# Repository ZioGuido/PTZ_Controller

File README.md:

# PTZ_Controller
Project for controlling PTZ camera via Arduino 

This project uses a Raspberry Pi Pico, an UART TTL to RS485 transceiver and a bunch of buttons to control PTZ cameras using the Pelco-D protocol.
I started this project because I was unhappy with the original controller we bought for controlling PTZ cameras in our TV studio. 
Those joystick controllers are made for the CCTV suirvellance cameras, they're not practical for the TV studio when recording or streaming live.

There were a series of issues:
- Too many button pushes to select a camera address (ESC, ADDR, number, ENTER)
- Too many button pushes to recall a preset (ESC, PRESET, number, ENTER)
- Joystick isn't precise
- Pan and Tilt speeds ramp up too rapidly using the joystick
- Buttons are too noisy
- LCD backlight goes off after a short while and you don't know which camera address it's on until you push a boutton

For these reasons I decided to make my owh controller without using a joystick, only big buttons and a couple of potentiometers.
Unfortunately, the camera we're using don't recognize the Zoom speed parameter from Pelco-D protocol, I should try writing a similar code but with Visca.
But for the remaining points, this controller is way better: silent buttons, just one push to select a camera (up to 4 addresses), 
just one push to recall a preset (up to 6 per camera), and you can vary Pan & Tilt speed while panning or tilting in a very smooth way.

One more thing:
This project makes use of 74HC595 and 74HC165 shift registers for controlling LEDs and reading button inputs.
These are serialized and share one common clock line, with the advantage of managing a high number of buttons and LEDs using only 4 pins of the CPU board.

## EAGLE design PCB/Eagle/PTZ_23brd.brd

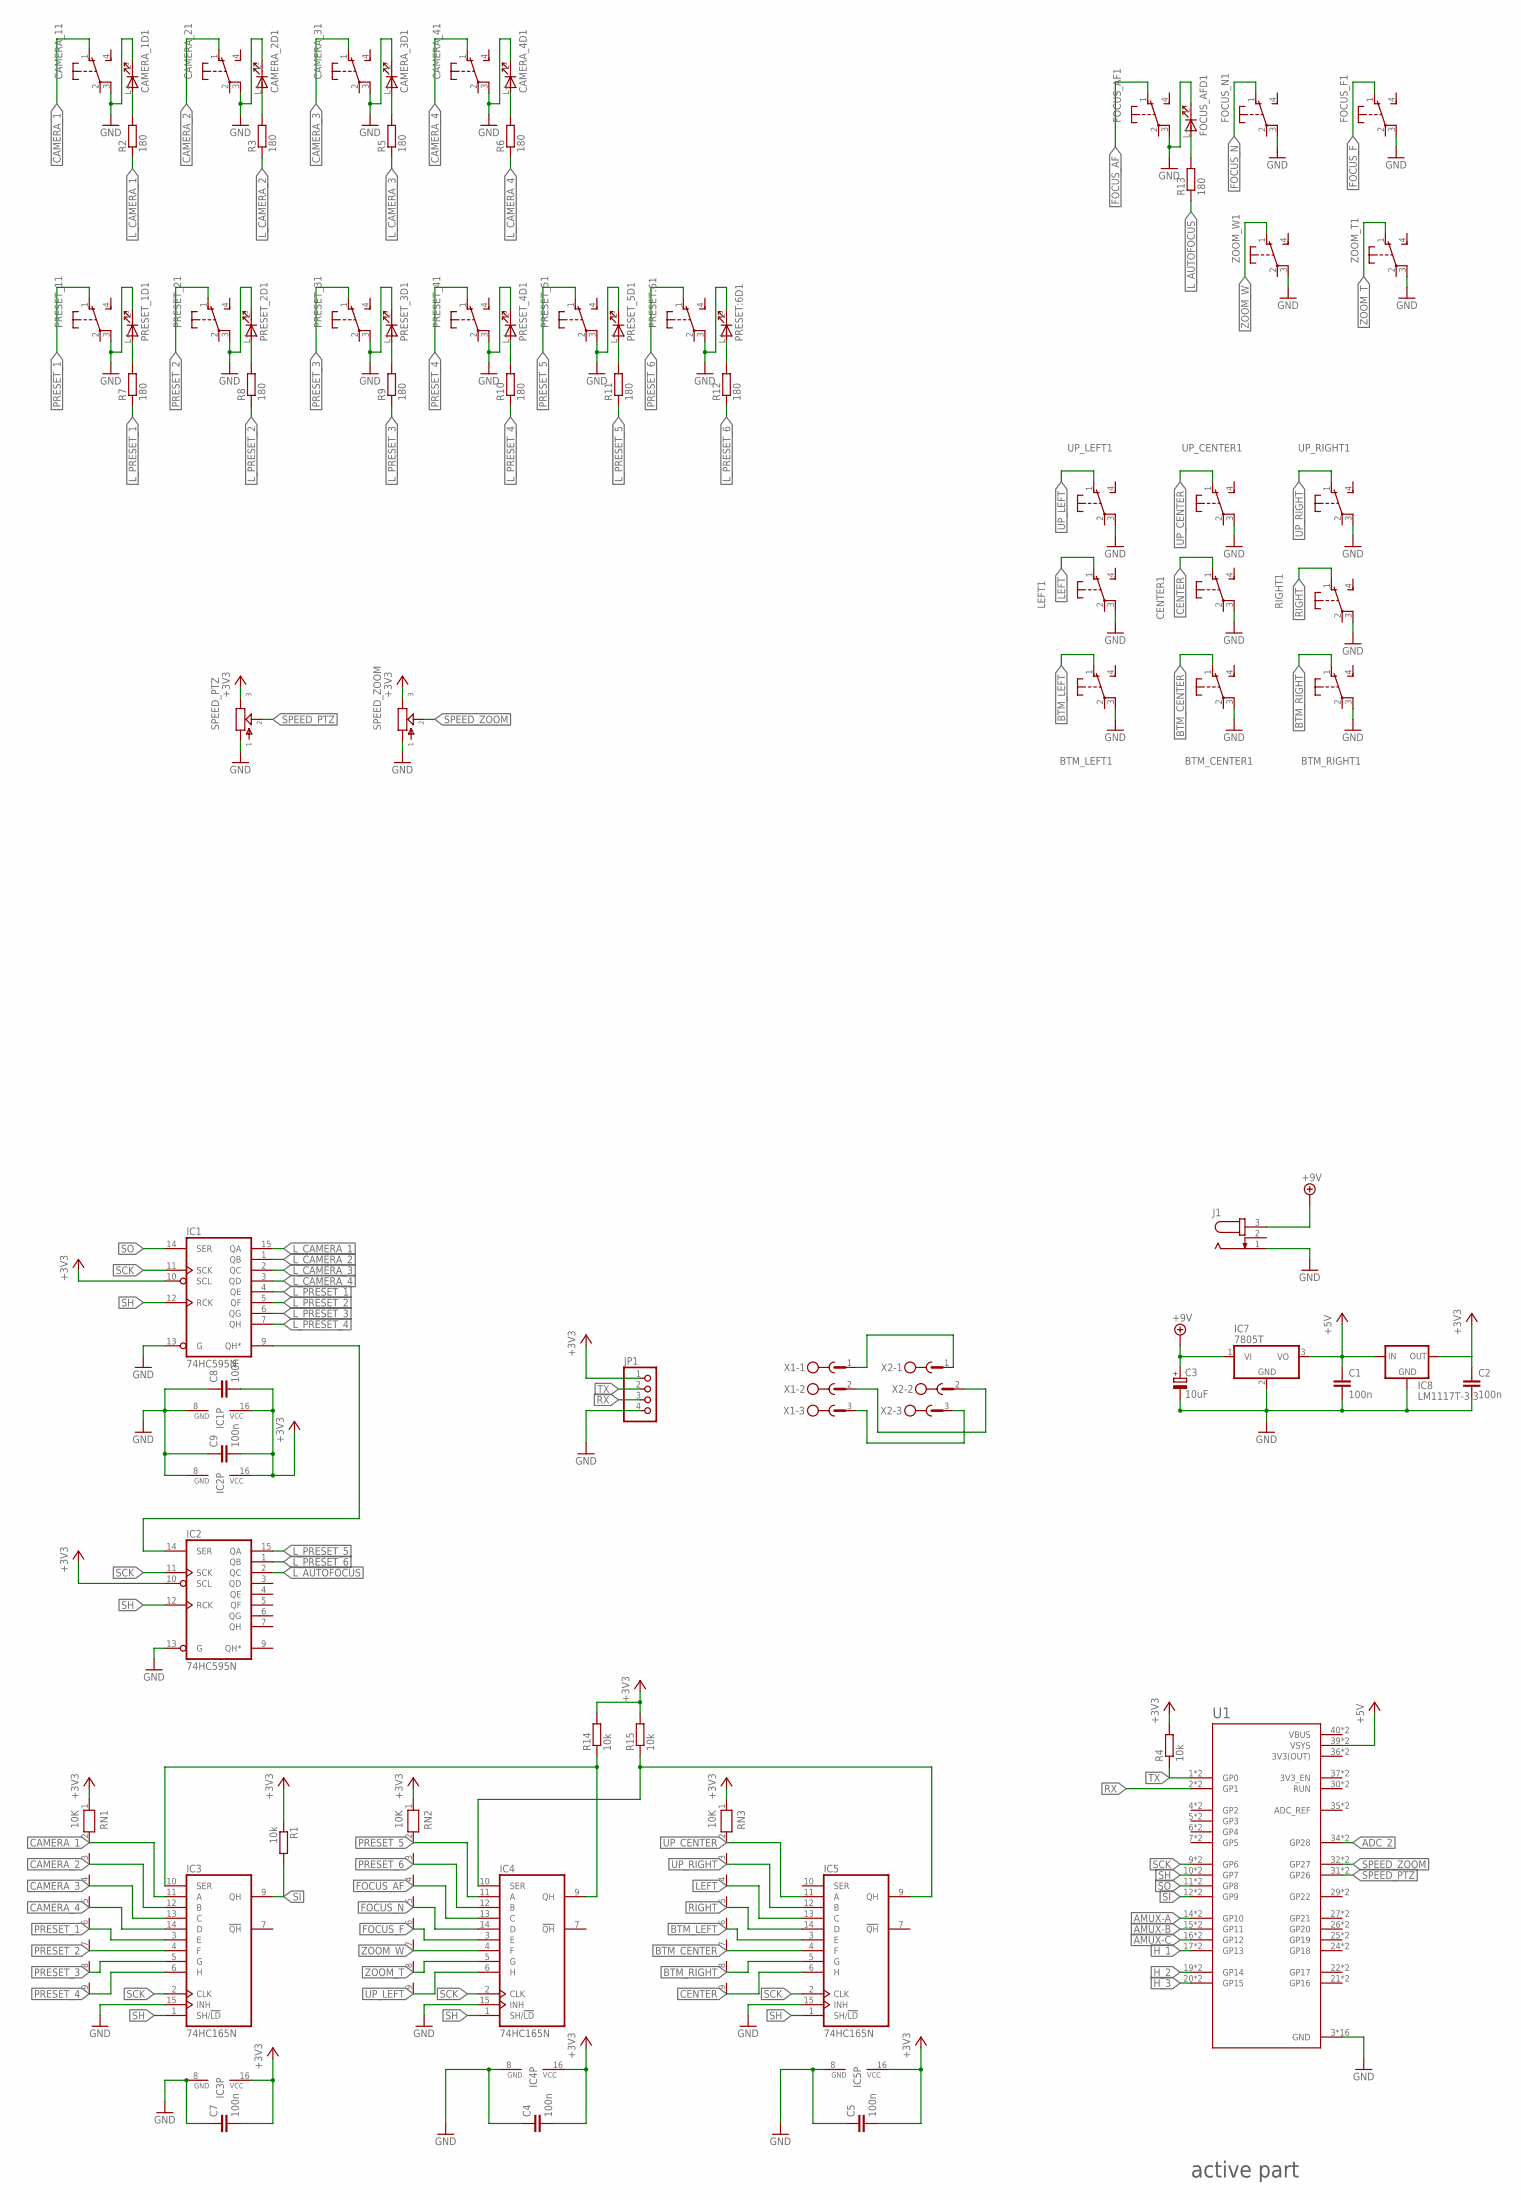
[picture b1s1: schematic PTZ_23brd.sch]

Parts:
BTM_CENTER: SWITCH-SHANPU_SRKLSHANPU_SPL; SWITCH-SHANPU_SPLG1YCS0014
BTM_LEFT: SWITCH-SHANPU_SRKLSHANPU_SPL; SWITCH-SHANPU_SPLG1YCS0014
BTM_RIGHT: SWITCH-SHANPU_SRKLSHANPU_SPL; SWITCH-SHANPU_SPLG1YCS0014
C1, C2, C4, C5, C7, C8, C9: 100n; C025-025X050
C3: 10uF; E2-5
CAMERA_1, CAMERA_2, CAMERA_3, CAMERA_4: SWITCH-SHANPU_SRKLSHANPU_SPL; SWITCH-SHANPU_SPLG1YCS0014
CENTER: SWITCH-SHANPU_SRKLSHANPU_SPL; SWITCH-SHANPU_SPLG1YCS0014
FOCUS_AF: SWITCH-SHANPU_SRKLSHANPU_SPL; SWITCH-SHANPU_SPLG1YCS0014
FOCUS_F: SWITCH-SHANPU_SRKLSHANPU_SPL; SWITCH-SHANPU_SPLG1YCS0014
FOCUS_N: SWITCH-SHANPU_SRKLSHANPU_SPL; SWITCH-SHANPU_SPLG1YCS0014
IC1, IC2: 74HC595N; DIL16
IC3, IC4, IC5: 74HC165N; DIL16
IC7: 7805T; TO220H
IC8: LM1117T-3.3; LM1117_TO220
J1: MOJO61_REAR42R_CON-JACK_JACK-PLUG; MOJO61_REAR42R_CON-JACK_2.1PCB
JP1: PINHD-1X4; 1X04
LEFT: SWITCH-SHANPU_SRKLSHANPU_SPL; SWITCH-SHANPU_SPLG1YCS0014
PRESET:6: SWITCH-SHANPU_SRKLSHANPU_SPL; SWITCH-SHANPU_SPLG1YCS0014
PRESET_1, PRESET_2, PRESET_3, PRESET_4, PRESET_5: SWITCH-SHANPU_SRKLSHANPU_SPL; SWITCH-SHANPU_SPLG1YCS0014
R1, R4, R14, R15: 10k; 0207/7
R2, R3, R5, R6, R7, R8, R9, R10, R11, R12, R13: 180; 0207/7
RIGHT: SWITCH-SHANPU_SRKLSHANPU_SPL; SWITCH-SHANPU_SPLG1YCS0014
RN1, RN2, RN3: 10K; RN-9
SPEED_PTZ: GM-POTS_POT-EU12MM; GM-POTS_RV120DF-40B1-(L)K
SPEED_ZOOM: GM-POTS_POT-EU12MM; GM-POTS_RV120DF-40B1-(L)K
U1: RPIPICO_RASPBERRY_PICO-NO_DEBUG; RPIPICO_PICO-PKG-NO_DEBUG
UP_CENTER: SWITCH-SHANPU_SRKLSHANPU_SPL; SWITCH-SHANPU_SPLG1YCS0014
UP_LEFT: SWITCH-SHANPU_SRKLSHANPU_SPL; SWITCH-SHANPU_SPLG1YCS0014
UP_RIGHT: SWITCH-SHANPU_SRKLSHANPU_SPL; SWITCH-SHANPU_SPLG1YCS0014
X1, X2: W232-3
ZOOM_T: SWITCH-SHANPU_SRKLSHANPU_SPL; SWITCH-SHANPU_SPLG1YCS0014
ZOOM_W: SWITCH-SHANPU_SRKLSHANPU_SPL; SWITCH-SHANPU_SPLG1YCS0014

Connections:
3V3(OUT): U1.36 (3V3(OUT)), U1.P$36 (3V3(OUT))
+3V3: C2.1, C4.2, C5.2, C7.2, C8.2, C9.2, IC1.10 (SCL), IC1.16 (VCC), IC2.10 (SCL), IC2.16 (VCC), IC3.16 (VCC), IC4.16 (VCC), IC5.16 (VCC), IC8.2 (OUT), JP1.1, R1.1, R4.2, R14.2, R15.2, RN1.1, RN2.1, RN3.1, SPEED_PTZ.3, SPEED_ZOOM.3
+5V: C1.1, IC7.3 (VO), IC8.3 (IN), U1.39 (VSYS), U1.P$39 (VSYS)
+9V: C3.+, IC7.1 (VI), J1.3
ADC_2: U1.34 (GP28), U1.P$34 (GP28)
AMUX-A: U1.14 (GP10), U1.P$14 (GP10)
AMUX-B: U1.15 (GP11), U1.P$15 (GP11)
AMUX-C: U1.16 (GP12), U1.P$16 (GP12)
BTM_CENTER: BTM_CENTER.1 (O), IC5.4 (F), RN3.7
BTM_LEFT: BTM_LEFT.1 (O), IC5.3 (E), RN3.6
BTM_RIGHT: BTM_RIGHT.1 (O), IC5.5 (G), RN3.8
CAMERA_1: CAMERA_1.1 (O), IC3.11 (A), RN1.2
CAMERA_2: CAMERA_2.1 (O), IC3.12 (B), RN1.3
CAMERA_3: CAMERA_3.1 (O), IC3.13 (C), RN1.4
CAMERA_4: CAMERA_4.1 (O), IC3.14 (D), RN1.5
CENTER: CENTER.1 (O), IC5.6 (H), RN3.9
FOCUS_AF: FOCUS_AF.1 (O), IC4.13 (C), RN2.4
FOCUS_F: FOCUS_F.1 (O), IC4.3 (E), RN2.6
FOCUS_N: FOCUS_N.1 (O), IC4.14 (D), RN2.5
GND: BTM_CENTER.3, BTM_LEFT.3, BTM_RIGHT.3, C1.2, C2.2, C3.-, C4.1, C5.1, C7.1, C8.1, C9.1, CAMERA_1.3, CAMERA_1.L- (C), CAMERA_2.3, CAMERA_2.L- (C), CAMERA_3.3, CAMERA_3.L- (C), CAMERA_4.3, CAMERA_4.L- (C), CENTER.3, FOCUS_AF.3, FOCUS_AF.L- (C), FOCUS_F.3, FOCUS_N.3, IC1.8 (GND), IC1.13 (G), IC2.8 (GND), IC2.13 (G), IC3.8 (GND), IC3.15 (INH), IC4.8 (GND), IC4.15 (INH), IC5.8 (GND), IC5.15 (INH), IC7.2 (GND), IC8.1 (GND), J1.1, JP1.4, LEFT.3, PRESET:6.3, PRESET:6.L- (C), PRESET_1.3, PRESET_1.L- (C), PRESET_2.3, PRESET_2.L- (C), PRESET_3.3, PRESET_3.L- (C), PRESET_4.3, PRESET_4.L- (C), PRESET_5.3, PRESET_5.L- (C), RIGHT.3, SPEED_PTZ.1, SPEED_ZOOM.1, U1.3 (GND), U1.8 (GND), U1.13 (GND), U1.18 (GND), U1.23 (GND), U1.28 (GND), U1.33 (GND), U1.38 (GND), U1.P$3 (GND), U1.P$8 (GND), U1.P$13 (GND), U1.P$18 (GND), U1.P$23 (GND), U1.P$28 (GND), U1.P$33 (GND), U1.P$38 (GND), UP_CENTER.3, UP_LEFT.3, UP_RIGHT.3, ZOOM_T.3, ZOOM_W.3
H_1: U1.17 (GP13), U1.P$17 (GP13)
H_2: U1.19 (GP14), U1.P$19 (GP14)
H_3: U1.20 (GP15), U1.P$20 (GP15)
LEFT: IC5.13 (C), LEFT.1 (O), RN3.4
L_AUTOFOCUS: IC2.2 (QC), R13.1
L_CAMERA_1: IC1.15 (QA), R2.1
L_CAMERA_2: IC1.1 (QB), R3.1
L_CAMERA_3: IC1.2 (QC), R5.1
L_CAMERA_4: IC1.3 (QD), R6.1
L_PRESET_1: IC1.4 (QE), R7.1
L_PRESET_2: IC1.5 (QF), R8.1
L_PRESET_3: IC1.6 (QG), R9.1
L_PRESET_4: IC1.7 (QH), R10.1
L_PRESET_5: IC2.15 (QA), R11.1
L_PRESET_6: IC2.1 (QB), R12.1
unnamed: IC1.9 (QH*), IC2.14 (SER)
unnamed: IC3.10 (SER), IC4.9 (QH), R14.1
unnamed: CAMERA_1.L+ (A), R2.2
unnamed: IC4.10 (SER), IC5.9 (QH), R15.1
unnamed: PRESET_2.L+ (A), R8.2
unnamed: X1.1, X2.1
unnamed: X1.2, X2.2
unnamed: X1.3, X2.3
unnamed: CAMERA_2.L+ (A), R3.2
unnamed: CAMERA_3.L+ (A), R5.2
unnamed: PRESET_3.L+ (A), R9.2
unnamed: CAMERA_4.L+ (A), R6.2
unnamed: FOCUS_AF.L+ (A), R13.2
unnamed: PRESET_4.L+ (A), R10.2
unnamed: PRESET_1.L+ (A), R7.2
unnamed: PRESET_5.L+ (A), R11.2
unnamed: PRESET:6.L+ (A), R12.2
PRESET_1: IC3.3 (E), PRESET_1.1 (O), RN1.6
PRESET_2: IC3.4 (F), PRESET_2.1 (O), RN1.7
PRESET_3: IC3.5 (G), PRESET_3.1 (O), RN1.8
PRESET_4: IC3.6 (H), PRESET_4.1 (O), RN1.9
PRESET_5: IC4.11 (A), PRESET_5.1 (O), RN2.2
PRESET_6: IC4.12 (B), PRESET:6.1 (O), RN2.3
RIGHT: IC5.14 (D), RIGHT.1 (O), RN3.5
RX: JP1.3, U1.2 (GP1), U1.P$2 (GP1)
SCK: IC1.11 (SCK), IC2.11 (SCK), IC3.2 (CLK), IC4.2 (CLK), IC5.2 (CLK), U1.9 (GP6), U1.P$9 (GP6)
SH: IC1.12 (RCK), IC2.12 (RCK), IC3.1 (SH/!LD), IC4.1 (SH/!LD), IC5.1 (SH/!LD), U1.10 (GP7), U1.P$10 (GP7)
SI: IC3.9 (QH), R1.2, U1.12 (GP9), U1.P$12 (GP9)
SO: IC1.14 (SER), U1.11 (GP8), U1.P$11 (GP8)
SPEED_PTZ: SPEED_PTZ.2, U1.31 (GP26), U1.P$31 (GP26)
SPEED_ZOOM: SPEED_ZOOM.2, U1.32 (GP27), U1.P$32 (GP27)
TX: JP1.2, R4.1, U1.1 (GP0), U1.P$1 (GP0)
UP_CENTER: IC5.11 (A), RN3.2, UP_CENTER.1 (O)
UP_LEFT: IC4.6 (H), RN2.9, UP_LEFT.1 (O)
UP_RIGHT: IC5.12 (B), RN3.3, UP_RIGHT.1 (O)
VBUS: U1.40 (VBUS), U1.P$40 (VBUS)
ZOOM_T: IC4.5 (G), RN2.8, ZOOM_T.1 (O)
ZOOM_W: IC4.4 (F), RN2.7, ZOOM_W.1 (O)

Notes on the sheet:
active part

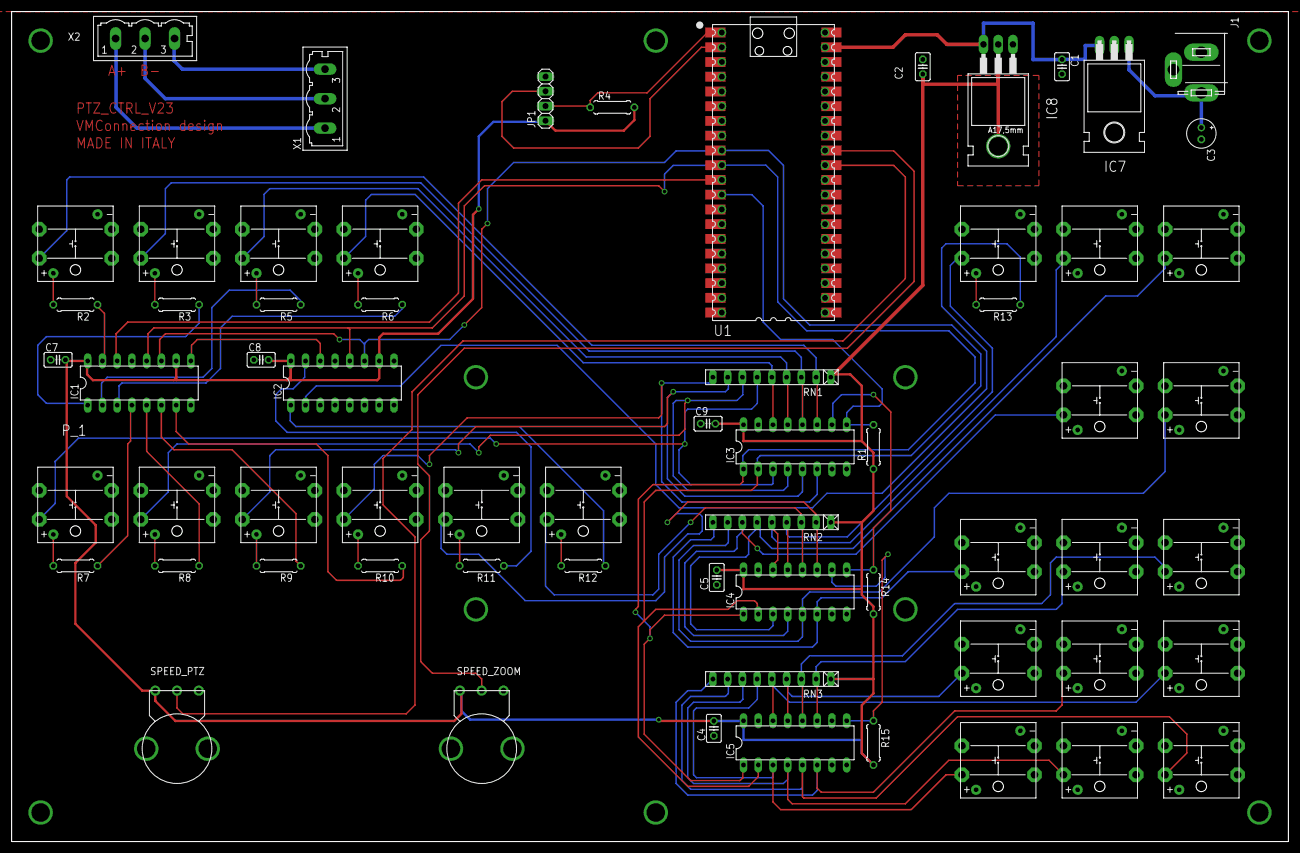
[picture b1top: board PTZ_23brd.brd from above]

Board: 2 copper layers, 220.0 x 143.0 mm, 64 parts (0 on the bottom side), 73 nets.

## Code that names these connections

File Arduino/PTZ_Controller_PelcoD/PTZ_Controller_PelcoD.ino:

/////////////////////////////////////////////////////////////////////////////////////
/////////////////////////////////////////////////////////////////////////////////////
// Controller for PTZ camera using PelcoD protocol
// Based on Raspberry Pi Pico + RS485 transceiver
// All buttons and LEDs are scanned/driven using 74HC165 & 74HC595 shift registers
//
// Code by Guido Scognamiglio - www.GenuineSoundware.com
// Last update: 21 July 2022
//


#include "../../GSiSRIO/SRIO.h"

GSiSRIO SRIO;
auto SRIOTimer = millis();
auto ButtonTimer = 0U;

byte PINS_CameraSelectBtn[] = { 0, 1, 2, 3 };
byte PINS_PresetBtn[] = { 4, 5, 6, 7, 8, 9 };
#define PIN_FOCUS_AUTO	10
#define PIN_FOCUS_F		11
#define PIN_FOCUS_N		12
#define PIN_ZOOM_W		13
#define PIN_ZOOM_T		14
#define PIN_UP_LEFT		15 
#define PIN_UP			16 
#define PIN_UP_RIGHT	17
#define PIN_LEFT		18
#define PIN_RIGHT		19 
#define PIN_DOWN_LEFT	20
#define PIN_DOWN		21
#define PIN_DOWN_RIGHT	22
byte PINS_PanTiltBtn[] = { 15, 16, 17, 18, 19, 20, 21, 22 };

// Remember: LED pins are reversed for each 595
byte LEDS_CameraSelect[] = { 7, 6, 5, 4 };
byte LEDS_Preset[] = { 3, 2, 1, 0, 15, 14 };
#define LED_FOCUS_AUTO	 13

byte Camera = 0;
byte Preset = 0;

byte CameraAddr = 1;
byte PT_Speed = 1;
byte ZOOM_Speed = 1;

byte PanningOrTilting = 0;

int ADC_Value[2] = { -1, -1 };
int ADC_Ports[2] = { A0, A1 };
int ADC_Select = 0;

int PresetPerCam[4] = { -1, -1, -1, -1 };

int BlinkLed = -1, BlinkT = 0, BlinkS = 0, BlinkC = 0;

void ReadADC(int port)
{
	// ADC Resolution is 12 bits
	auto value = 0; 
	for (int i = 0; i < 10; ++i) value += analogRead(ADC_Ports[port]);
	value /= 10;

	auto diff = abs(value - ADC_Value[port]);
	if (diff <= 8) return;
	ADC_Value[port] = value;

	//Serial.printf("ADC n. %d - Value = %d\n", port, value);
	
	// Pot 0 = Pan/Tilt speed
	if (port == 0)
	{
		int newSpeed = value >> 6; // Pan/Tilt speed is 6 bits 0x00 ~ 0x3F
		if (PT_Speed != newSpeed)
		{
			PT_Speed = newSpeed;

			if (PanningOrTilting > 0)
				SendPelcoD(CameraAddr, 0x00, PanningOrTilting, PT_Speed, PT_Speed);
		}
	}
	
	// Pot 1 = Zoom speed	
	if (port == 1)
	{
		 auto newSpeed = value >> 10; // only 2 bits!
		 if (ZOOM_Speed != newSpeed)
		 {
			 ZOOM_Speed = newSpeed;
			 SendPelcoD(CameraAddr, 0x00, 0x25, 0x00, ZOOM_Speed);
		 }
	}
	//Serial.printf("PT_Speed = %d - ZOOM_Speed = %d\n", PT_Speed, ZOOM_Speed);
}

void SendPelcoD(uint8_t addr, uint8_t cmd1, uint8_t cmd2, uint8_t data1, uint8_t data2)
{
	int sum = (addr + cmd1 + cmd2 + data1 + data2) % 0x100;
	uint8_t cmd[7] = { 0xFF, addr, cmd1, cmd2, data1, data2, sum };
	Serial1.write(cmd, 7);

	Serial.printf("Pelco-D: 0x%02X 0x%02X 0x%02X 0x%02X 0x%02X 0x%02X 0x%02X\n", cmd[0], cmd[1], cmd[2], cmd[3], cmd[4], cmd[5], cmd[6]);
}

void SelectCamera(byte cam)
{
	Serial.printf("Set Camera n. %d\n", cam + 1);

	Camera = cam;
	CameraAddr = Camera + 1;
	
	for (byte c = 0; c < 4; c++)
		SRIO.DOUT_PinSet(LEDS_CameraSelect[c], Camera == c);

	for (auto p = 0; p < 6; ++p)
		SRIO.DOUT_PinSet(LEDS_Preset[p], PresetPerCam[Camera] == p);
}

void NoPreset()
{
	PresetPerCam[Camera] = -1;

	for (auto p = 0; p < 6; ++p)
		SRIO.DOUT_PinSet(LEDS_Preset[p], 0);
}

void SavePreset(byte pNum)
{
	Serial.printf("Save Presetn n. %d\n", pNum + 1);
	
	SendPelcoD(CameraAddr, 0x00, 0x03, 0x00, pNum);
	PresetPerCam[Camera] = pNum;

	for (auto p = 0; p < 6; ++p)
		SRIO.DOUT_PinSet(LEDS_Preset[p], 0);

	BlinkLed = LEDS_Preset[pNum];
}

void RecallPreset(byte pNum)
{
	Serial.printf("Recall Presetn n. %d\n", pNum + 1);
	
	ButtonTimer = 0;
	PresetPerCam[Camera] = pNum;
	SendPelcoD(CameraAddr, 0x00, 0x07, 0x00, pNum);

	for (auto p = 0; p < 6; ++p)
		SRIO.DOUT_PinSet(LEDS_Preset[p], p == pNum);
}

void DIN_Notify(uint8_t pin, uint8_t value)
{
	// Button down
	if (value == 0)
	{
		switch (pin)
		{
		case PIN_UP_LEFT:		SendPelcoD(CameraAddr, 0x00, 0x0C, PT_Speed, PT_Speed); NoPreset(); PanningOrTilting = 0x0C; break;
		case PIN_UP:			SendPelcoD(CameraAddr, 0x00, 0x08, PT_Speed, PT_Speed); NoPreset(); PanningOrTilting = 0x08; break;
		case PIN_UP_RIGHT:		SendPelcoD(CameraAddr, 0x00, 0x0A, PT_Speed, PT_Speed); NoPreset(); PanningOrTilting = 0x0A; break;
		case PIN_LEFT:			SendPelcoD(CameraAddr, 0x00, 0x04, PT_Speed, PT_Speed); NoPreset(); PanningOrTilting = 0x04; break;
		case PIN_RIGHT:			SendPelcoD(CameraAddr, 0x00, 0x02, PT_Speed, PT_Speed); NoPreset(); PanningOrTilting = 0x02; break;
		case PIN_DOWN_LEFT:		SendPelcoD(CameraAddr, 0x00, 0x14, PT_Speed, PT_Speed); NoPreset(); PanningOrTilting = 0x14; break;
		case PIN_DOWN:			SendPelcoD(CameraAddr, 0x00, 0x10, PT_Speed, PT_Speed); NoPreset(); PanningOrTilting = 0x10; break;
		case PIN_DOWN_RIGHT:	SendPelcoD(CameraAddr, 0x00, 0x12, PT_Speed, PT_Speed); NoPreset(); PanningOrTilting = 0x12; break;

		case PIN_FOCUS_AUTO:	
			SendPelcoD(CameraAddr, 0x00, 0x2B, 0, 0);
			SRIO.DOUT_PinSet(LED_FOCUS_AUTO, 1);
			break;
		case PIN_FOCUS_N:		
			SRIO.DOUT_PinSet(LED_FOCUS_AUTO, 0);
			SendPelcoD(CameraAddr, 0x00, 0x2B, 0, 1);
			SendPelcoD(CameraAddr, 0x01, 0x00, 0, 0); 
			break;
		case PIN_FOCUS_F:		
			SRIO.DOUT_PinSet(LED_FOCUS_AUTO, 0);
			SendPelcoD(CameraAddr, 0x00, 0x2B, 0, 1);
			SendPelcoD(CameraAddr, 0x00, 0x80, 0, 0);
			break;

		case PIN_ZOOM_W:		
			SendPelcoD(CameraAddr, 0x00, 0x40, 0x00, 0x00);
			NoPreset();
			break;
		case PIN_ZOOM_T:		
			SendPelcoD(CameraAddr, 0x00, 0x20, 0x00, 0x00);
			NoPreset();
			break;

		default:
			for (auto c : PINS_CameraSelectBtn)
				if (pin == c)
					return SelectCamera(c);
			
			for (auto p : PINS_PresetBtn)
				if (pin == p)
				{
					ButtonTimer = 500; 
					return;
				}
		}
	}

	// Button up
	else
	{
		// Recall Preset
		for (auto p = 0; p < 6; ++p)
			if (pin == PINS_PresetBtn[p] && ButtonTimer > 1)
				return RecallPreset(p);

		// If one of the Pan/Tilt buttons is still depressed when another button has been released, take action
		for (auto p : PINS_PanTiltBtn)
			if (SRIO.DIN_PinGet(p) == 0)
				return DIN_Notify(p, 0);
		
		// Stop any movement when a button is released
		SendPelcoD(CameraAddr, 0, 0, 0, 0);
		PanningOrTilting = 0;
	}
}

void setup()
{
	Serial.begin(115200);
	Serial1.begin(9600);

	SRIO.Init(DIN_Notify);
	SRIO.SRIO_NumberSet(3);
	SRIO.DebounceSet(16);

	analogReadResolution(10); delay(100); analogReadResolution(12);

	SelectCamera(0);
	DIN_Notify(PIN_FOCUS_AUTO, 0);
}

void loop()
{
	// Run every millisecond
	if (millis() - SRIOTimer > 1)
	{
		SRIOTimer = millis();

		ReadADC(ADC_Select);
		ADC_Select = ADC_Select == 0 ? 1 : 0;

		SRIO.Run();

		// Button long press for saving presets?
		if (ButtonTimer > 0) ButtonTimer--;
		if (ButtonTimer == 1)
		{
			ButtonTimer = 0;
			for (auto p = 0; p < 6; ++p)
				if (SRIO.DIN_PinGet(PINS_PresetBtn[p]) == 0)
					return SavePreset(p);
		}

		if (BlinkLed >= 0)
		{
			if (++BlinkT >= 25)
			{
				BlinkT = 0;
				SRIO.DOUT_PinSet(BlinkLed, BlinkS);
				BlinkS = ~BlinkS;

				if (++BlinkC > 5)
				{
					BlinkC = 0;
					BlinkLed = -1;
					SRIO.DOUT_PinSet(BlinkLed, 1);
				}
			}
		}
	}
}

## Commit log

2022-08-06 Added GSi SRIO library
